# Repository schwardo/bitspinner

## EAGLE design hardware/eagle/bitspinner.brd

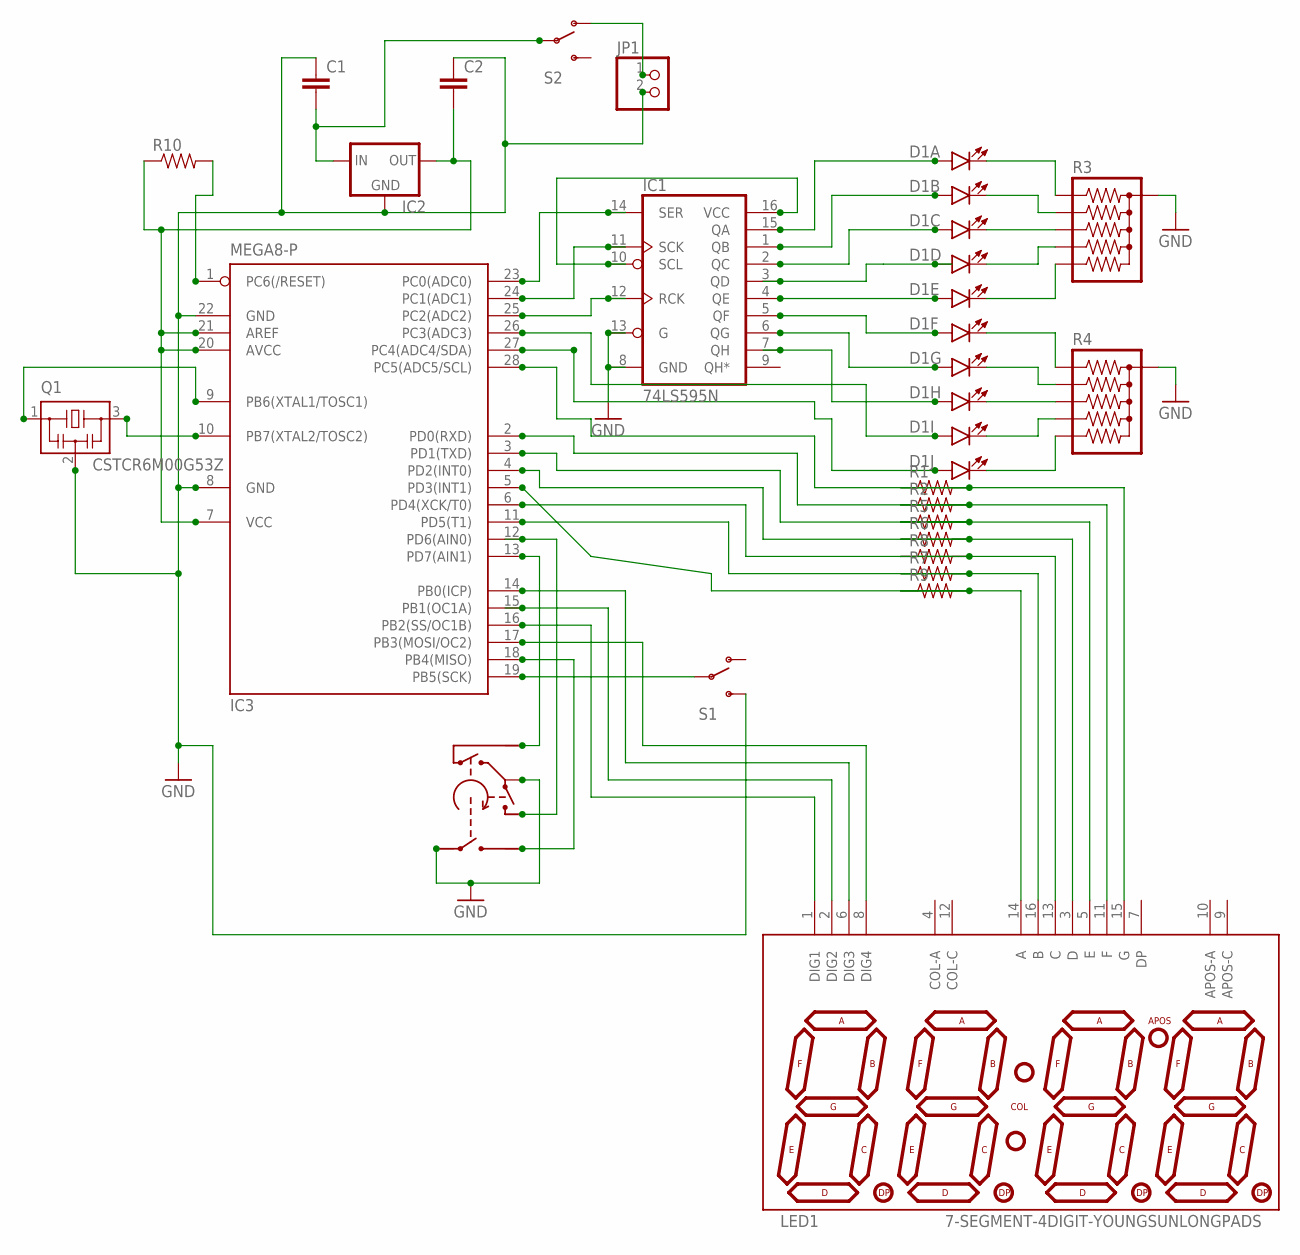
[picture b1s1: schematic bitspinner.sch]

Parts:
C1, C2: CAPPTH; CAP-PTH-SMALL
D1: LED_BARGRAPH_10; LED_BARGAPH_10
IC1: 74LS595N; DIL16
IC2: V_REG_78XXSIDE; 78XXL
IC3: MEGA8-P; DIL28-3
JP1: PINHD-1X2; 1X02
LED1: 7-SEGMENT-4DIGIT-YOUNGSUNLONGPADS; 7-SEGMENT-4DIGIT-YOUNGSUN-LONGPADS
Q1: CSTCR6M00G53Z; CSTCR6M
R1, R2, R5, R6, R7, R8, R9, R10: RESISTORAXIAL-0.3; AXIAL-0.3
R3, R4: RPACK-BUSSED-SIP-PTH-5; RPACK-SIP-PTH-5
S1, S2: SWITCH-SPSTPTH; SWITCH-SPDT
U$1: ALPHA-ROT-ENCODER; TW-700198

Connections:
GND: C1.1, C2.1, IC1.8 (GND), IC1.13 (G), IC2.GND, IC3.8 (GND), IC3.22 (GND), JP1.2, Q1.2, R3.P$1 (1), R4.P$1 (1), S1.3 (S), U$1.P2 (COM), U$1.P4 (S1)
unnamed: D1.20 (C), R3.P$2 (2)
unnamed: D1.19 (C), R3.P$3 (3)
unnamed: D1.18 (C), R3.P$4 (4)
unnamed: D1.17 (C), R3.P$5 (5)
unnamed: D1.16 (C), R3.P$6 (6)
unnamed: D1.1 (A), IC1.15 (QA)
unnamed: D1.15 (C), R4.P$2 (2)
unnamed: D1.11 (C), R4.P$6 (6)
unnamed: D1.13 (C), R4.P$4 (4)
unnamed: D1.4 (A), IC1.3 (QD)
unnamed: D1.2 (A), IC1.1 (QB)
unnamed: D1.3 (A), IC1.2 (QC)
unnamed: IC1.10 (SCL), IC1.16 (VCC)
unnamed: D1.5 (A), IC1.4 (QE)
unnamed: IC1.14 (SER), IC3.23 (PC0(ADC0))
unnamed: D1.14 (C), R4.P$3 (3)
unnamed: D1.12 (C), R4.P$5 (5)
unnamed: D1.6 (A), IC1.5 (QF)
unnamed: D1.7 (A), IC1.6 (QG)
unnamed: D1.8 (A), IC1.7 (QH)
unnamed: IC1.11 (SCK), IC3.24 (PC1(ADC1))
unnamed: IC1.12 (RCK), IC3.25 (PC2(ADC2))
unnamed: C1.2, IC2.IN, S2.2
unnamed: IC3.28 (PC5(ADC5/SCL)), R1.P$2 (2)
unnamed: IC3.2 (PD0(RXD)), R2.P$2 (2)
unnamed: IC3.3 (PD1(TXD)), R5.P$2 (2)
unnamed: LED1.14 (A), R9.P$1 (1)
unnamed: LED1.16 (B), R7.P$1 (1)
unnamed: LED1.13 (C), R8.P$1 (1)
unnamed: LED1.3 (D), R6.P$1 (1)
unnamed: LED1.5 (E), R5.P$1 (1)
unnamed: LED1.11 (F), R2.P$1 (1)
unnamed: LED1.15 (G), R1.P$1 (1)
unnamed: IC3.4 (PD2(INT0)), R6.P$2 (2)
unnamed: IC3.6 (PD4(XCK/T0)), R8.P$2 (2)
unnamed: IC3.11 (PD5(T1)), R7.P$2 (2)
unnamed: IC3.5 (PD3(INT1)), R9.P$2 (2)
unnamed: IC3.16 (PB2(SS/OC1B)), LED1.1 (DIG1)
unnamed: IC3.19 (PB5(SCK)), S1.2
unnamed: JP1.1, S2.1 (O)
unnamed: D1.9 (A), IC3.26 (PC3(ADC3))
unnamed: D1.10 (A), IC3.27 (PC4(ADC4/SDA))
unnamed: IC3.18 (PB4(MISO)), U$1.P5 (S2)
unnamed: IC3.15 (PB1(OC1A)), LED1.2 (DIG2)
unnamed: IC3.14 (PB0(ICP)), LED1.6 (DIG3)
unnamed: IC3.17 (PB3(MOSI/OC2)), LED1.8 (DIG4)
unnamed: IC3.1 (PC6(/RESET)), R10.P$2 (2)
unnamed: IC3.12 (PD6(AIN0)), U$1.P1 (B)
unnamed: C2.2, IC2.OUT, IC3.7 (VCC), IC3.20 (AVCC), IC3.21 (AREF), R10.P$1 (1)
unnamed: IC3.9 (PB6(XTAL1/TOSC1)), Q1.1
unnamed: IC3.10 (PB7(XTAL2/TOSC2)), Q1.3
unnamed: IC3.13 (PD7(AIN1)), U$1.P3 (A)

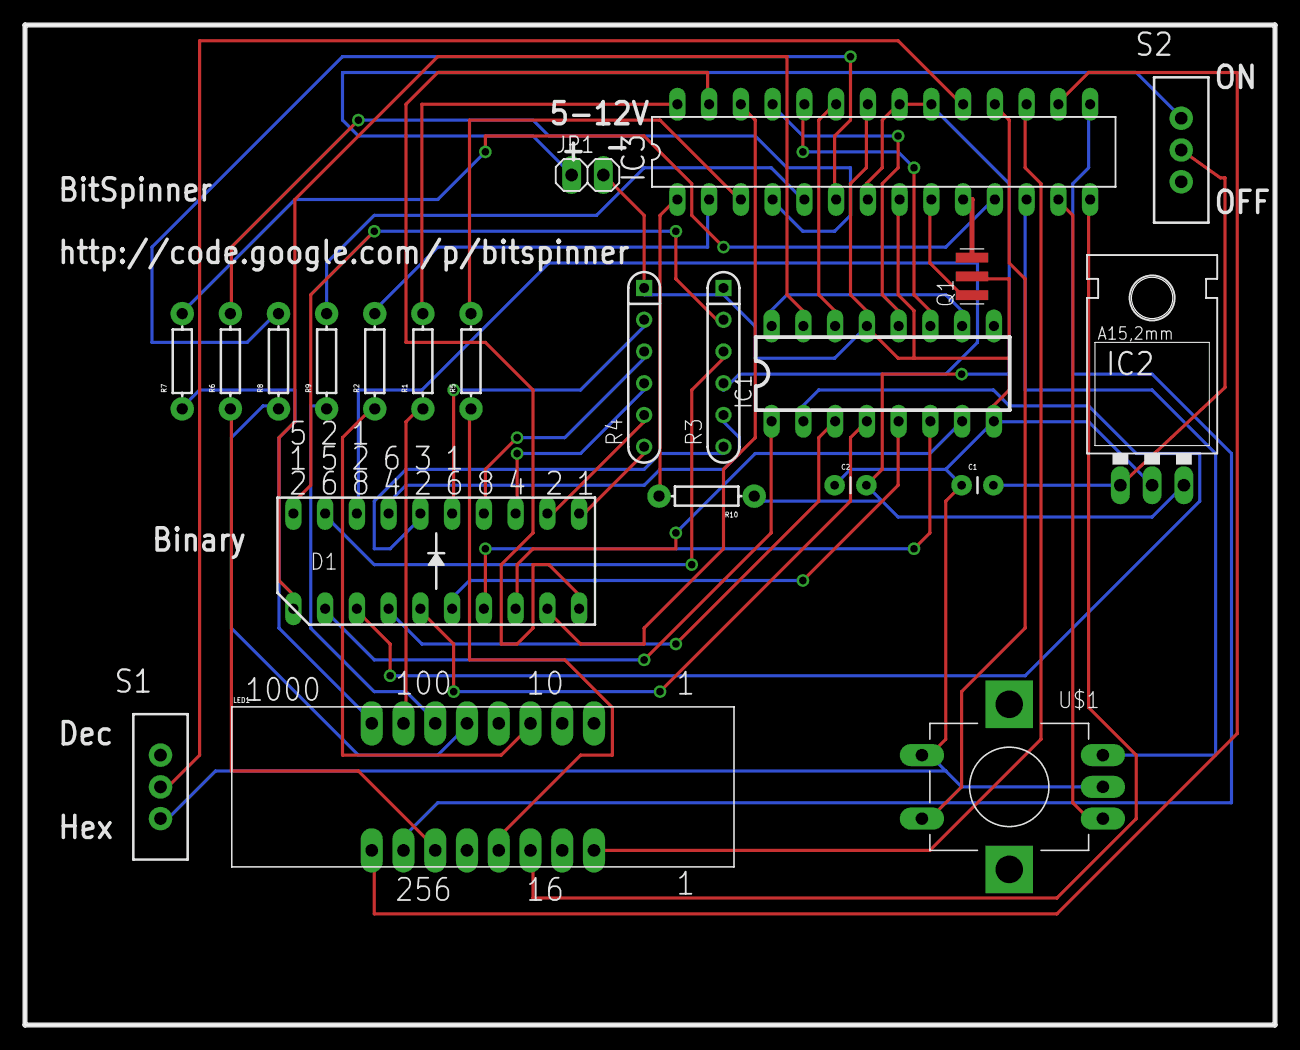
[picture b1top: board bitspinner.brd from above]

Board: 2 copper layers, 100.0 x 80.0 mm, 22 parts (0 on the bottom side), 53 nets.

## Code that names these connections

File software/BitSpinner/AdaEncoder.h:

// We use 4-character tabstops, so IN VIM:  <esc>:set ts=4
// ...that's: ESCAPE key, colon key, then "s-e-t SPACE key t-s-=-4"
/*
 AdaEncoder.h - A library for reading Lady Ada's or 
 Sparkfun's rotary encoder.
 Should work for any rotary encoder with 2 pins (4 states).

 Version 0.3 Thu Sep 22 20:11:31 CDT 2011
 	Updated to save the old value of the SREG prior to cli().
 Version 0.4 Sun Oct  9 12:09:17 CDT 2011
    Includes cppfix.h, so that we can use the new() operator with PinChangeInt-0.3 (and above).
 Version 0.5 Wed Feb 29 07:30:23 CST 2012
	Shipped without PinChangeInt, so we don't stomp on PinChangeInt if the user has both libraries.
	Includes the LIBCALL_PINCHANGEINT macro for work with PinChangeInt v1.70beta (and newer).
	Cleaned up some of the #includes.
	Included a copy of the gpl in the zip file, like a good citizen.  The file is gpl.txt.
*/

/*
  Copyright 2011 Michael Schwager (aka, "GreyGnome")

	This program is free software: you can redistribute it and/or modify
    it under the terms of the GNU General Public License as published by
    the Free Software Foundation, either version 3 of the License, or
    (at your option) any later version.

    This program is distributed in the hope that it will be useful,
    but WITHOUT ANY WARRANTY; without even the implied warranty of
    MERCHANTABILITY or FITNESS FOR A PARTICULAR PURPOSE.  See the
    GNU General Public License for more details.

    You should have received a copy of the GNU General Public License
    along with this program.  If not, see <http://www.gnu.org/licenses/>.

	Questions?  Send mail to mschwage@gmail.com

*/

/* Behavior goes like this:
 * 11 is the detent position for an encoder.  So the encoder will go through an order like this:
 *   11 <=> 01 <=> 00 <=> 10 <=> 11    OR    11 <=> 10 <=> 00 <=> 01 <=> 11
 * depending on direction.  The <=> represent a possible bounce situation.  Therefore, we keep track of the
 * encoder behavior in a binary number called (appropriately enough) encoder.  Encoder has 8 bits.
 * 
 * The process starts when we get an interrupt and read the encoder pins.
 * - Reading: 11 is either a bounce back to start, or the final reading:
 * 	- If encoder is currently xxxx0001, you have advanced CW.
 * 	- If encoder is currently xxxx0010, you have advanced CCW.
 *	- otherwise, you'd simply bounced.  No advance.
 *	- "encoder" is set to xxxx1111.
 * - Reading: 01 or 10:
 *	- If "encoder" is currently xxxx1111, set it to 1101 or 1110, appropriately.
 *	- If "encoder" is xxxx00xy, you'd either bounced or moved to the next position, which means we get closer to detent.  No effect.
 * - Reading: 00: we are in the middle.  AND encoder with xxxx0011
 */

#undef DEBUG

#ifndef AdaEncoder_h
#define AdaEncoder_h

#if defined(ARDUINO) && ARDUINO >= 100
  #include <Arduino.h>
#else
  #include <pins_arduino.h>
  #include <wiring.h>
#endif

//  The Pin map below is copyright by the Arduino people.  I include it here so I can remember stuff as I code.
// ATMEL ATMEGA8 & 168 / ARDUINO
// //
// //                  +-\/-+
// //            PC6  1|    |28  PC5 (AI 5)
// //      (D 0) PD0  2|    |27  PC4 (AI 4)
// //      (D 1) PD1  3|    |26  PC3 (AI 3)
// //      (D 2) PD2  4|    |25  PC2 (AI 2)
// // PWM+ (D 3) PD3  5|    |24  PC1 (AI 1)
// //      (D 4) PD4  6|    |23  PC0 (AI 0)
// //            VCC  7|    |22  GND
// //            GND  8|    |21  AREF
// //            PB6  9|    |20  AVCC
// //            PB7 10|    |19  PB5 (D 13)
// // PWM+ (D 5) PD5 11|    |18  PB4 (D 12)
// // PWM+ (D 6) PD6 12|    |17  PB3 (D 11) PWM
// //      (D 7) PD7 13|    |16  PB2 (D 10) PWM
// //      (D 8) PB0 14|    |15  PB1 (D 9) PWM
// //                  +----+
// 
// const static uint8_t A0 = 14;
// const static uint8_t A1 = 15;
// const static uint8_t A2 = 16;
// const static uint8_t A3 = 17;
// const static uint8_t A4 = 18;
// const static uint8_t A5 = 19;
// const static uint8_t A6 = 20;
// const static uint8_t A7 = 21;
//
// Macros to find pins:
// #define digitalPinToPort(P) ( pgm_read_byte( digital_pin_to_port_PGM + (P) ) )
// #define digitalPinToBitMask(P) ( pgm_read_byte( digital_pin_to_bit_mask_PGM + (P) ) )
// #define digitalPinToTimer(P) ( pgm_read_byte( digital_pin_to_timer_PGM + (P) ) )
// #define analogInPinToBit(P) (P)
// #define portOutputRegister(P) ( (volatile uint8_t *)( pgm_read_word( port_to_output_PGM + (P))) )
// #define portInputRegister(P) ( (volatile uint8_t *)( pgm_read_word( port_to_input_PGM + (P))) )
// #define portModeRegister(P) ( (volatile uint8_t *)( pgm_read_word( port_to_mode_PGM + (P))) )

static int count;

struct encoder {
    volatile uint8_t* port;

    uint8_t bitA;
    uint8_t bitB;

    uint8_t turning;    // Flag to keep track of turning state
    int8_t clicks;      // Counter to indicate cumulative clicks in either direction
    int8_t direction;   // indicator

    char id;

    encoder *next;
};

class AdaEncoder {
 public:

	static void debugMessage();

    /*
     * 
     */
	static encoder *getFirstEncoder();

    /* 
     * Add a new encoder 
     * Params :
     * pinA			CW pin  (Arduino pin number)
     * pinB			CCW pin
	 *
     */
	static void addEncoder(char id, uint8_t pinA, uint8_t pinB);

	static void attachInterrupt(uint8_t pinA, uint8_t pinB);

	static void encoderInterrupt();

	static void turnOffPWM(uint8_t timer);

	static encoder *genie();

	static encoder *genie(int8_t *clicks, char *id); // GEt Next Indicated Encoder - gets the next encoder with non-zero clicks

 private:

	AdaEncoder(); // prevents anyone from instantiating an object of this class

	static encoder *currentEncoder;

};

#endif	//AdaEncoder.h

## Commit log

2012-05-05 Initial version.
2012-05-05 Adding schematics and layout for rev1 of the board.
2012-05-05 Adding gerbers for rev1.
2012-05-06 Stop trying to PWM the last binary digits -- these output pins do not support PWM. Various other minor cleanups.
2012-05-06 Adding images.
2012-05-06 New image for resonator.
2012-05-06 Add regulator.
2012-05-06 Add encoder.
2012-05-06 Add box to encoder.
2012-05-26 Fix counter incrementing.
2015-03-14 Migrating wiki contents from Google Code

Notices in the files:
parts and their libraries:
SparkFun: Licensing: CC v3.0 Share-Alike You are welcome to use this library for commercial purposes.
